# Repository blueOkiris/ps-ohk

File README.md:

# Polymath-Studio One-Handed Keyboard

## Description

Type with only one hand

Designed around

1) the most common letters used
2) relationships between sounds
3) the shape of a left hand
4) practicality

The PS-OHK (pronounced "psawk" [p͡sɑk̚]) aims to be the ultimate one-handed typing experience all without special modifiers (a standard key count) and a layout that is relatively easy to get used to.

## Build and Upload

Dependencies:

- arduino-cli
- make
- sdcc
- ch55xtool
- libusb

Build with `make -C fw`

Hold program button down, plug in, let go of program button, and run `make -C fw upload` within 3 seconds

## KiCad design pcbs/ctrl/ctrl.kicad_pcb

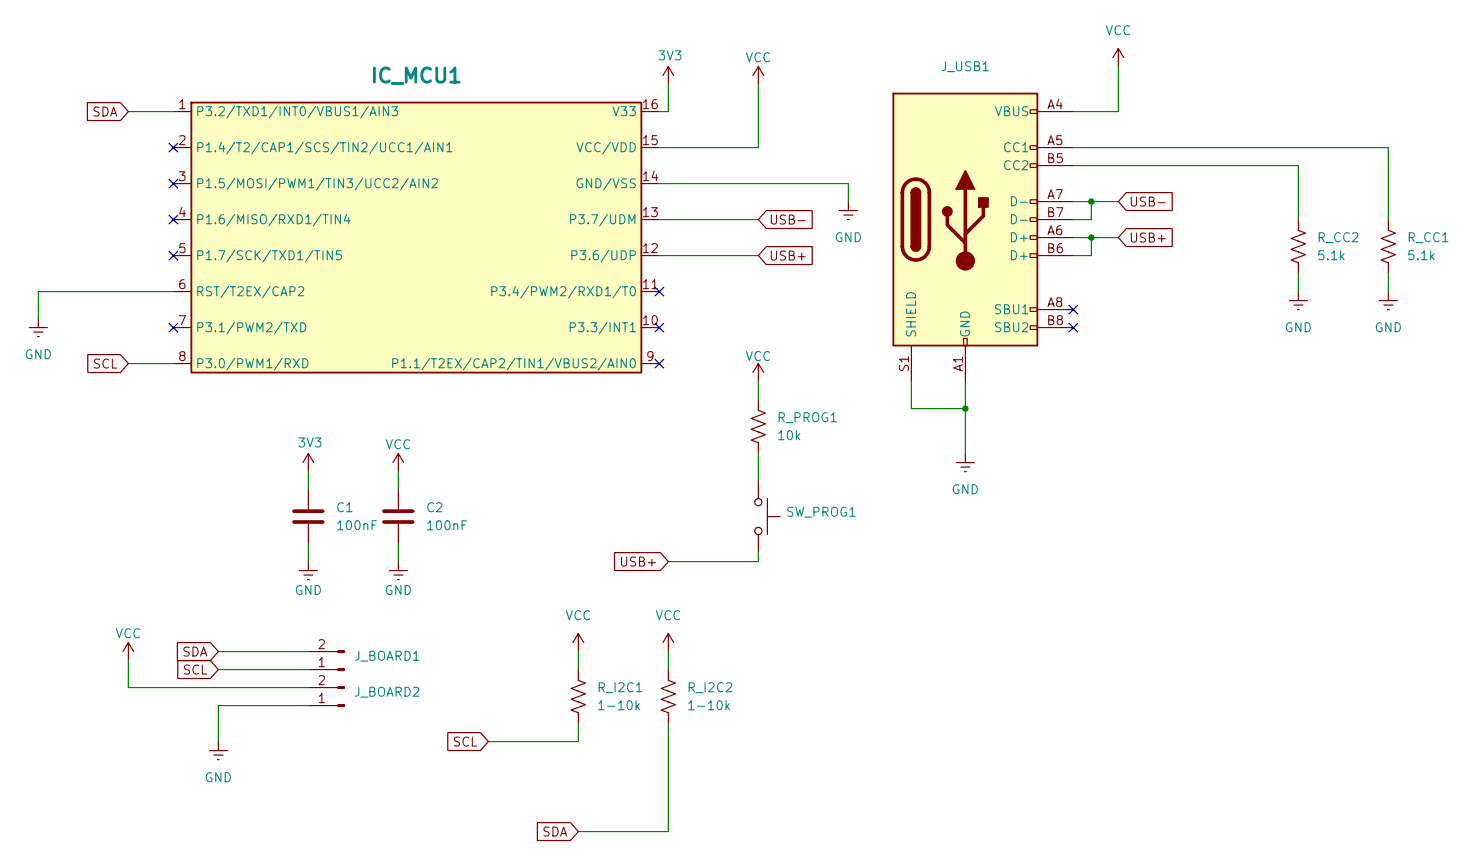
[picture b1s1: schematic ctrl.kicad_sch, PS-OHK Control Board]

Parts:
C1, C2: 100nF; C_0603_1608Metric
IC_MCU1: SOIC-16_3.9x9.9mm_Pitch1.27mm
J_BOARD1, J_BOARD2: PinHeader_1x02_P2.54mm_Vertical
J_USB1: USB_C_Receptacle_HCTL_HC-TYPE-C-16P-01A
R_CC1, R_CC2: 5.1k; R_0603_1608Metric
R_I2C1, R_I2C2: 1-10k; R_0603_1608Metric
R_PROG1: 10k; R_0603_1608Metric
SW_PROG1: SW_PUSH_6mm

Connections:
3V3: C1.1, IC_MCU1.16 (V33)
GND: C1.2, C2.2, IC_MCU1.6 (RST/T2EX/CAP2), IC_MCU1.14 (GND/VSS), J_BOARD2.1, J_USB1.A1 (GND), J_USB1.A12 (GND), J_USB1.B1 (GND), J_USB1.B12 (GND), J_USB1.S1 (SHIELD), R_CC1.2, R_CC2.2
unnamed: J_USB1.A5 (CC1), R_CC1.1
unnamed: J_USB1.B5 (CC2), R_CC2.1
unnamed: R_PROG1.2, SW_PROG1.1
SCL: IC_MCU1.8 (P3.0/PWM1/RXD), J_BOARD1.1, R_I2C1.2
SDA: IC_MCU1.1 (P3.2/TXD1/INT0/VBUS1/AIN3), J_BOARD1.2, R_I2C2.2
USB+: IC_MCU1.12 (P3.6/UDP), J_USB1.A6 (D+), J_USB1.B6 (D+), SW_PROG1.2
USB-: IC_MCU1.13 (P3.7/UDM), J_USB1.A7 (D-), J_USB1.B7 (D-)
VCC: C2.1, IC_MCU1.15 (VCC/VDD), J_BOARD2.2, J_USB1.A4 (VBUS), J_USB1.A9 (VBUS), J_USB1.B4 (VBUS), J_USB1.B9 (VBUS), R_I2C1.1, R_I2C2.1, R_PROG1.1

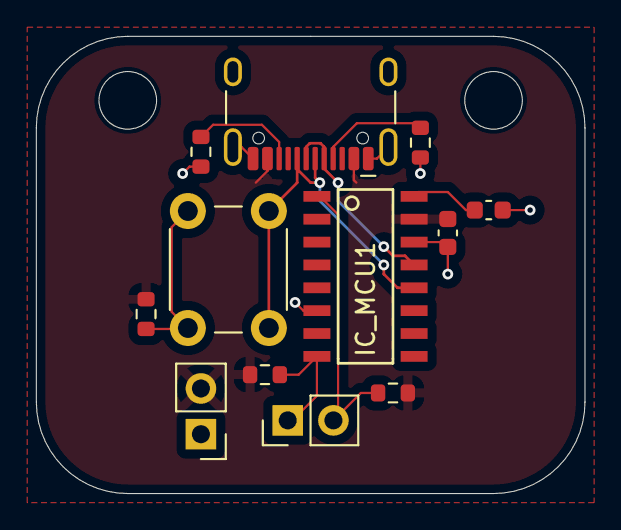
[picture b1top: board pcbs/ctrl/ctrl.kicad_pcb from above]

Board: 2 copper layers, 30.5 x 25.4 mm, 12 parts (0 on the bottom side), 10 nets.

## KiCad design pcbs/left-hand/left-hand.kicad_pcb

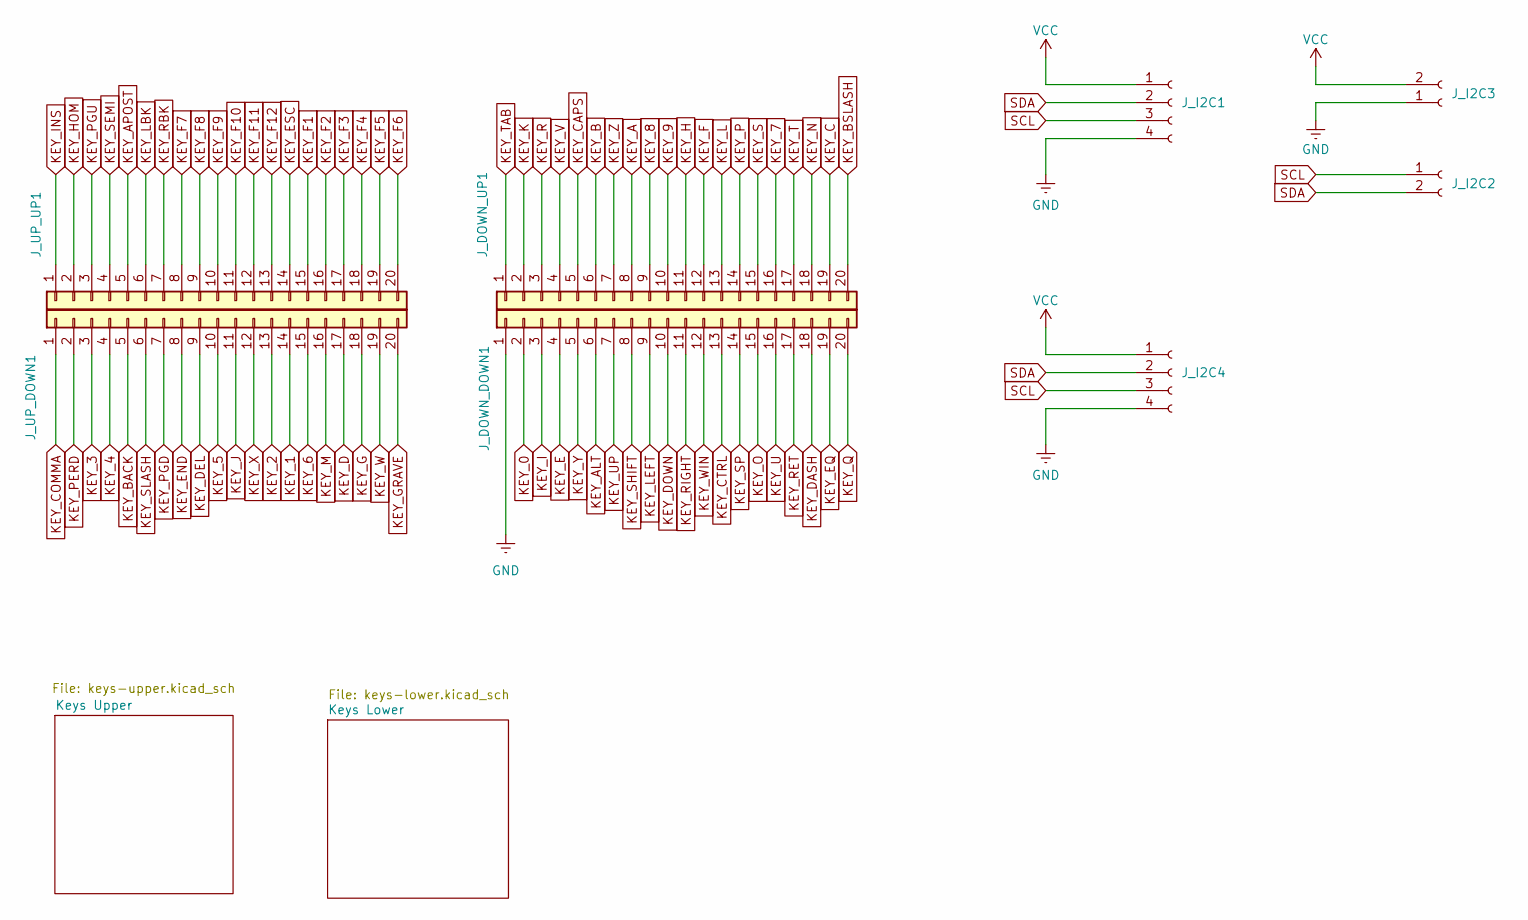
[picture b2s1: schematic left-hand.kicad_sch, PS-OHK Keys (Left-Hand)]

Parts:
J_DOWN_DOWN1: Conn_01x20; PinHeader_1x20_P2.54mm_Vertical
J_DOWN_UP1: Conn_01x20; PinHeader_1x20_P2.54mm_Vertical
J_I2C1, J_I2C4: Conn_01x04_Socket; PinHeader_1x04_P2.54mm_Vertical
J_I2C2, J_I2C3: Conn_01x04_Socket; PinHeader_1x02_P2.54mm_Vertical
J_UP_DOWN1: Conn_01x20; PinHeader_1x20_P2.54mm_Vertical
J_UP_UP1: Conn_01x20; PinHeader_1x20_P2.54mm_Vertical

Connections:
GND: J_DOWN_DOWN1.1, J_I2C1.4, J_I2C3.1, J_I2C4.4; also elsewhere on the board
KEY_0: J_DOWN_DOWN1.2; also elsewhere on the board
KEY_1: J_UP_DOWN1.14; also elsewhere on the board
KEY_2: J_UP_DOWN1.13; also elsewhere on the board
KEY_3: J_UP_DOWN1.3; also elsewhere on the board
KEY_4: J_UP_DOWN1.4; also elsewhere on the board
KEY_5: J_UP_DOWN1.10; also elsewhere on the board
KEY_6: J_UP_DOWN1.15; also elsewhere on the board
KEY_7: J_DOWN_UP1.16; also elsewhere on the board
KEY_8: J_DOWN_UP1.9; also elsewhere on the board
KEY_9: J_DOWN_UP1.10; also elsewhere on the board
KEY_A: J_DOWN_UP1.8; also elsewhere on the board
KEY_ALT: J_DOWN_DOWN1.6; also elsewhere on the board
KEY_APOST: J_UP_UP1.5; also elsewhere on the board
KEY_B: J_DOWN_UP1.6; also elsewhere on the board
KEY_BACK: J_UP_DOWN1.5; also elsewhere on the board
KEY_BSLASH: J_DOWN_UP1.20; also elsewhere on the board
KEY_C: J_DOWN_UP1.19; also elsewhere on the board
KEY_CAPS: J_DOWN_UP1.5; also elsewhere on the board
KEY_COMMA: J_UP_DOWN1.1; also elsewhere on the board
KEY_CTRL: J_DOWN_DOWN1.13; also elsewhere on the board
KEY_D: J_UP_DOWN1.17; also elsewhere on the board
KEY_DASH: J_DOWN_DOWN1.18; also elsewhere on the board
KEY_DEL: J_UP_DOWN1.9; also elsewhere on the board
KEY_DOWN: J_DOWN_DOWN1.10; also elsewhere on the board
KEY_E: J_DOWN_DOWN1.4; also elsewhere on the board
KEY_END: J_UP_DOWN1.8; also elsewhere on the board
KEY_EQ: J_DOWN_DOWN1.19; also elsewhere on the board
KEY_ESC: J_UP_UP1.14; also elsewhere on the board
KEY_F: J_DOWN_UP1.12; also elsewhere on the board
KEY_F1: J_UP_UP1.15; also elsewhere on the board
KEY_F2: J_UP_UP1.16; also elsewhere on the board
KEY_F3: J_UP_UP1.17; also elsewhere on the board
KEY_F4: J_UP_UP1.18; also elsewhere on the board
KEY_F5: J_UP_UP1.19; also elsewhere on the board
KEY_F6: J_UP_UP1.20; also elsewhere on the board
KEY_F7: J_UP_UP1.8; also elsewhere on the board
KEY_F8: J_UP_UP1.9; also elsewhere on the board
KEY_F9: J_UP_UP1.10; also elsewhere on the board
KEY_F10: J_UP_UP1.11; also elsewhere on the board
KEY_F11: J_UP_UP1.12; also elsewhere on the board
KEY_F12: J_UP_UP1.13; also elsewhere on the board
KEY_G: J_UP_DOWN1.18; also elsewhere on the board
KEY_GRAVE: J_UP_DOWN1.20; also elsewhere on the board
KEY_H: J_DOWN_UP1.11; also elsewhere on the board
KEY_HOM: J_UP_UP1.2; also elsewhere on the board
KEY_I: J_DOWN_DOWN1.3; also elsewhere on the board
KEY_INS: J_UP_UP1.1; also elsewhere on the board
KEY_J: J_UP_DOWN1.11; also elsewhere on the board
KEY_K: J_DOWN_UP1.2; also elsewhere on the board
KEY_L: J_DOWN_UP1.13; also elsewhere on the board
KEY_LBK: J_UP_UP1.6; also elsewhere on the board
KEY_LEFT: J_DOWN_DOWN1.9; also elsewhere on the board
KEY_M: J_UP_DOWN1.16; also elsewhere on the board
KEY_N: J_DOWN_UP1.18; also elsewhere on the board
KEY_O: J_DOWN_DOWN1.15; also elsewhere on the board
KEY_P: J_DOWN_UP1.14; also elsewhere on the board
KEY_PERD: J_UP_DOWN1.2; also elsewhere on the board
KEY_PGD: J_UP_DOWN1.7; also elsewhere on the board
KEY_PGU: J_UP_UP1.3; also elsewhere on the board
KEY_Q: J_DOWN_DOWN1.20; also elsewhere on the board
KEY_R: J_DOWN_UP1.3; also elsewhere on the board
KEY_RBK: J_UP_UP1.7; also elsewhere on the board
KEY_RET: J_DOWN_DOWN1.17; also elsewhere on the board
KEY_RIGHT: J_DOWN_DOWN1.11; also elsewhere on the board
KEY_S: J_DOWN_UP1.15; also elsewhere on the board
KEY_SEMI: J_UP_UP1.4; also elsewhere on the board
KEY_SHIFT: J_DOWN_DOWN1.8; also elsewhere on the board
KEY_SLASH: J_UP_DOWN1.6; also elsewhere on the board
KEY_SP: J_DOWN_DOWN1.14; also elsewhere on the board
KEY_T: J_DOWN_UP1.17; also elsewhere on the board
KEY_TAB: J_DOWN_UP1.1; also elsewhere on the board
KEY_U: J_DOWN_DOWN1.16; also elsewhere on the board
KEY_UP: J_DOWN_DOWN1.7; also elsewhere on the board
KEY_V: J_DOWN_UP1.4; also elsewhere on the board
KEY_W: J_UP_DOWN1.19; also elsewhere on the board
KEY_WIN: J_DOWN_DOWN1.12; also elsewhere on the board
KEY_X: J_UP_DOWN1.12; also elsewhere on the board
KEY_Y: J_DOWN_DOWN1.5; also elsewhere on the board
KEY_Z: J_DOWN_UP1.7; also elsewhere on the board
SCL: J_I2C1.3, J_I2C2.1, J_I2C4.3
SDA: J_I2C1.2, J_I2C2.2, J_I2C4.2
VCC: J_I2C1.1, J_I2C3.2, J_I2C4.1

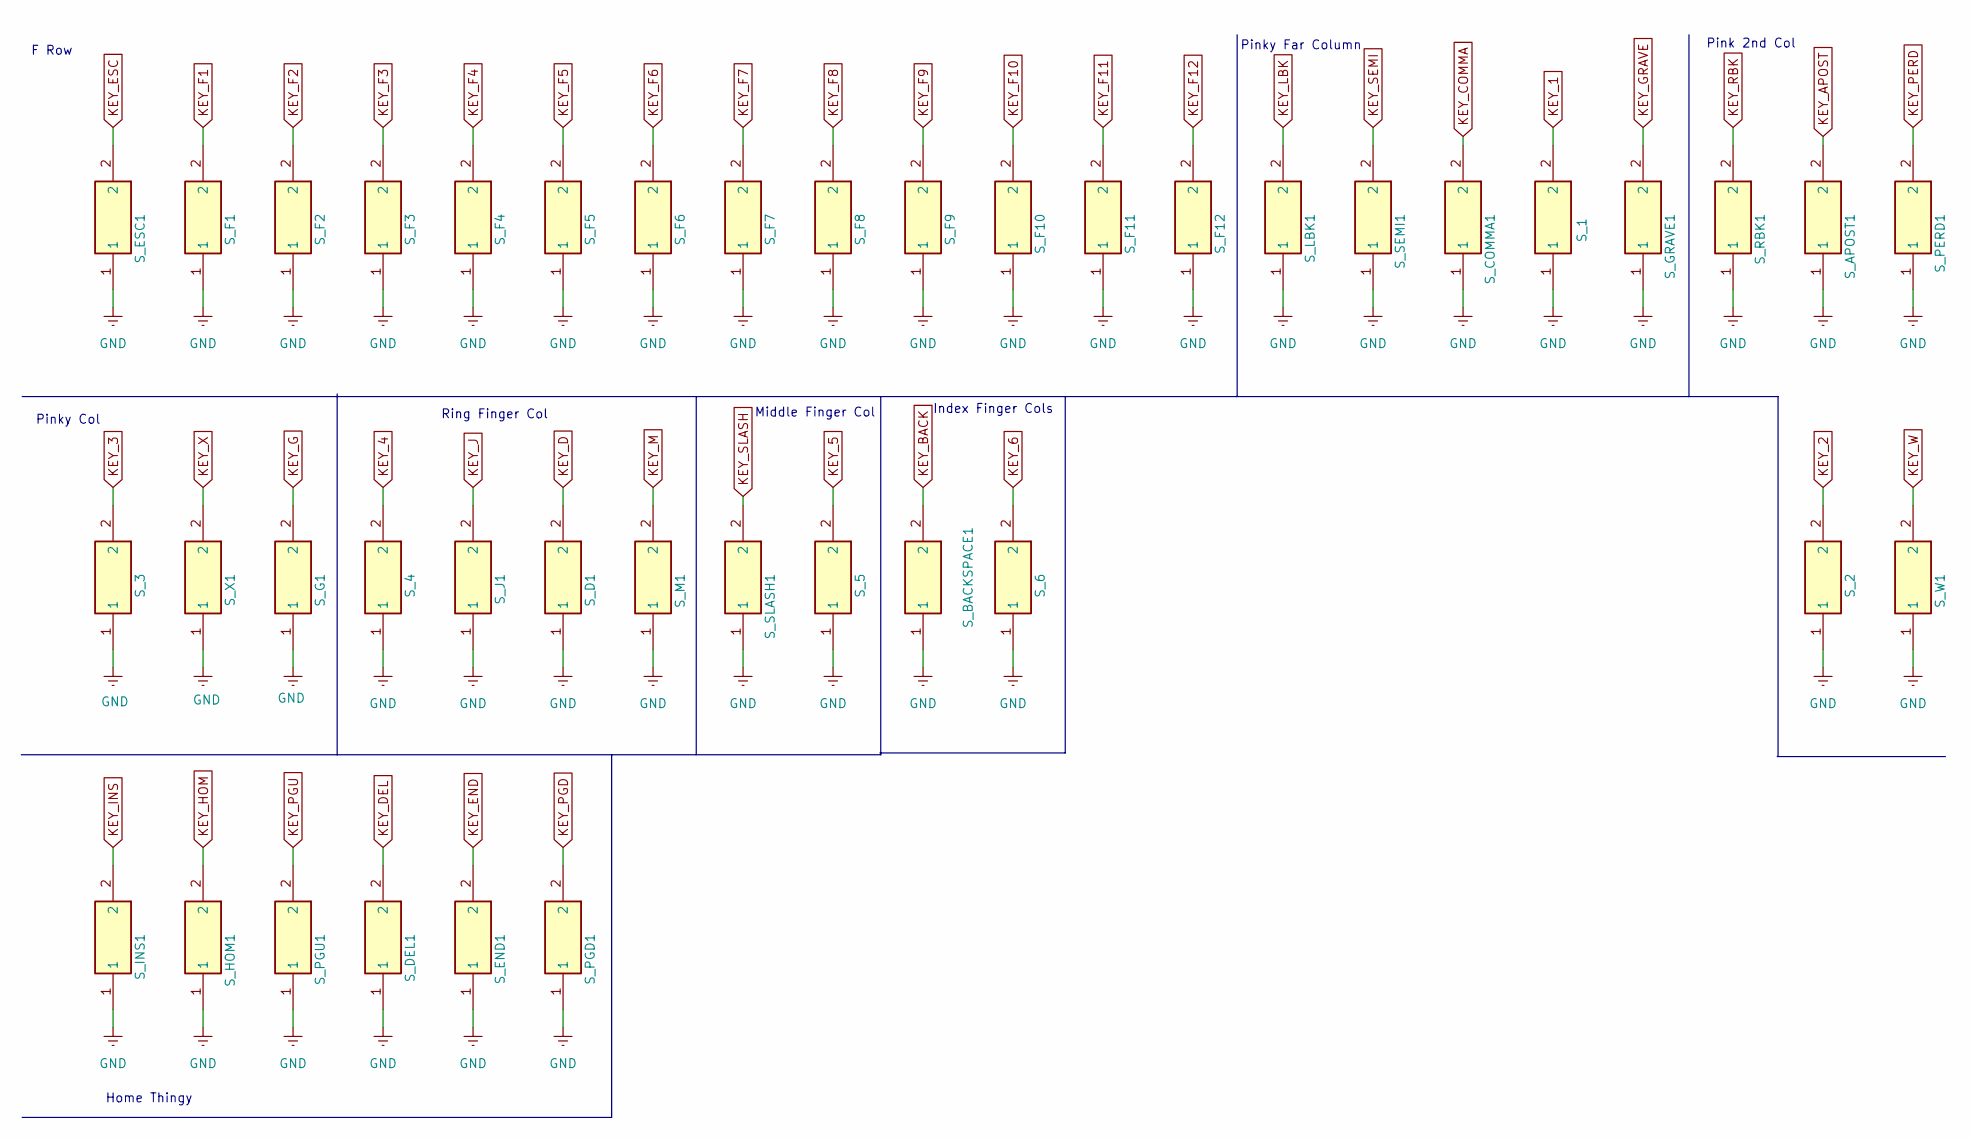
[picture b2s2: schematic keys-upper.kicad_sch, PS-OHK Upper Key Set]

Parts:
S_1, S_2, S_3, S_4, S_5, S_6: COM13834; Mouser Part Number 474-COM-13834
S_APOST1: COM13834; Mouser Part Number 474-COM-13834
S_BACKSPACE1: COM13834; Mouser Part Number 474-COM-13834
S_COMMA1: COM13834; Mouser Part Number 474-COM-13834
S_D1: COM13834; Mouser Part Number 474-COM-13834
S_DEL1: COM13834; Mouser Part Number 474-COM-13834
S_END1: COM13834; Mouser Part Number 474-COM-13834
S_ESC1: COM13834; Mouser Part Number 474-COM-13834
S_F1, S_F2, S_F3, S_F4, S_F5, S_F6, S_F7, S_F8, S_F9, S_F10, S_F11, S_F12: COM13834; Mouser Part Number 474-COM-13834
S_G1: COM13834; Mouser Part Number 474-COM-13834
S_GRAVE1: COM13834; Mouser Part Number 474-COM-13834
S_HOM1: COM13834; Mouser Part Number 474-COM-13834
S_INS1: COM13834; Mouser Part Number 474-COM-13834
S_J1: COM13834; Mouser Part Number 474-COM-13834
S_LBK1: COM13834; Mouser Part Number 474-COM-13834
S_M1: COM13834; Mouser Part Number 474-COM-13834
S_PERD1: COM13834; Mouser Part Number 474-COM-13834
S_PGD1: COM13834; Mouser Part Number 474-COM-13834
S_PGU1: COM13834; Mouser Part Number 474-COM-13834
S_RBK1: COM13834; Mouser Part Number 474-COM-13834
S_SEMI1: COM13834; Mouser Part Number 474-COM-13834
S_SLASH1: COM13834; Mouser Part Number 474-COM-13834
S_W1: COM13834; Mouser Part Number 474-COM-13834
S_X1: COM13834; Mouser Part Number 474-COM-13834

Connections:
GND: S_1.1, S_2.1, S_3.1, S_4.1, S_5.1, S_6.1, S_APOST1.1, S_BACKSPACE1.1, S_COMMA1.1, S_D1.1, S_DEL1.1, S_END1.1, S_ESC1.1, S_F1.1, S_F2.1, S_F3.1, S_F4.1, S_F5.1, S_F6.1, S_F7.1, S_F8.1, S_F9.1, S_F10.1, S_F11.1, S_F12.1, S_G1.1, S_GRAVE1.1, S_HOM1.1, S_INS1.1, S_J1.1, S_LBK1.1, S_M1.1, S_PERD1.1, S_PGD1.1, S_PGU1.1, S_RBK1.1, S_SEMI1.1, S_SLASH1.1, S_W1.1, S_X1.1; also elsewhere on the board
KEY_1: S_1.2; also elsewhere on the board
KEY_2: S_2.2; also elsewhere on the board
KEY_3: S_3.2; also elsewhere on the board
KEY_4: S_4.2; also elsewhere on the board
KEY_5: S_5.2; also elsewhere on the board
KEY_6: S_6.2; also elsewhere on the board
KEY_APOST: S_APOST1.2; also elsewhere on the board
KEY_BACK: S_BACKSPACE1.2; also elsewhere on the board
KEY_COMMA: S_COMMA1.2; also elsewhere on the board
KEY_D: S_D1.2; also elsewhere on the board
KEY_DEL: S_DEL1.2; also elsewhere on the board
KEY_END: S_END1.2; also elsewhere on the board
KEY_ESC: S_ESC1.2; also elsewhere on the board
KEY_F1: S_F1.2; also elsewhere on the board
KEY_F2: S_F2.2; also elsewhere on the board
KEY_F3: S_F3.2; also elsewhere on the board
KEY_F4: S_F4.2; also elsewhere on the board
KEY_F5: S_F5.2; also elsewhere on the board
KEY_F6: S_F6.2; also elsewhere on the board
KEY_F7: S_F7.2; also elsewhere on the board
KEY_F8: S_F8.2; also elsewhere on the board
KEY_F9: S_F9.2; also elsewhere on the board
KEY_F10: S_F10.2; also elsewhere on the board
KEY_F11: S_F11.2; also elsewhere on the board
KEY_F12: S_F12.2; also elsewhere on the board
KEY_G: S_G1.2; also elsewhere on the board
KEY_GRAVE: S_GRAVE1.2; also elsewhere on the board
KEY_HOM: S_HOM1.2; also elsewhere on the board
KEY_INS: S_INS1.2; also elsewhere on the board
KEY_J: S_J1.2; also elsewhere on the board
KEY_LBK: S_LBK1.2; also elsewhere on the board
KEY_M: S_M1.2; also elsewhere on the board
KEY_PERD: S_PERD1.2; also elsewhere on the board
KEY_PGD: S_PGD1.2; also elsewhere on the board
KEY_PGU: S_PGU1.2; also elsewhere on the board
KEY_RBK: S_RBK1.2; also elsewhere on the board
KEY_SEMI: S_SEMI1.2; also elsewhere on the board
KEY_SLASH: S_SLASH1.2; also elsewhere on the board
KEY_W: S_W1.2; also elsewhere on the board
KEY_X: S_X1.2; also elsewhere on the board

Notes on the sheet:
Pink 2nd Col
Middle Finger Col
Pinky Far Column
Pinky Col
Ring Finger Col
Index Finger Cols
Home Thingy
F Row

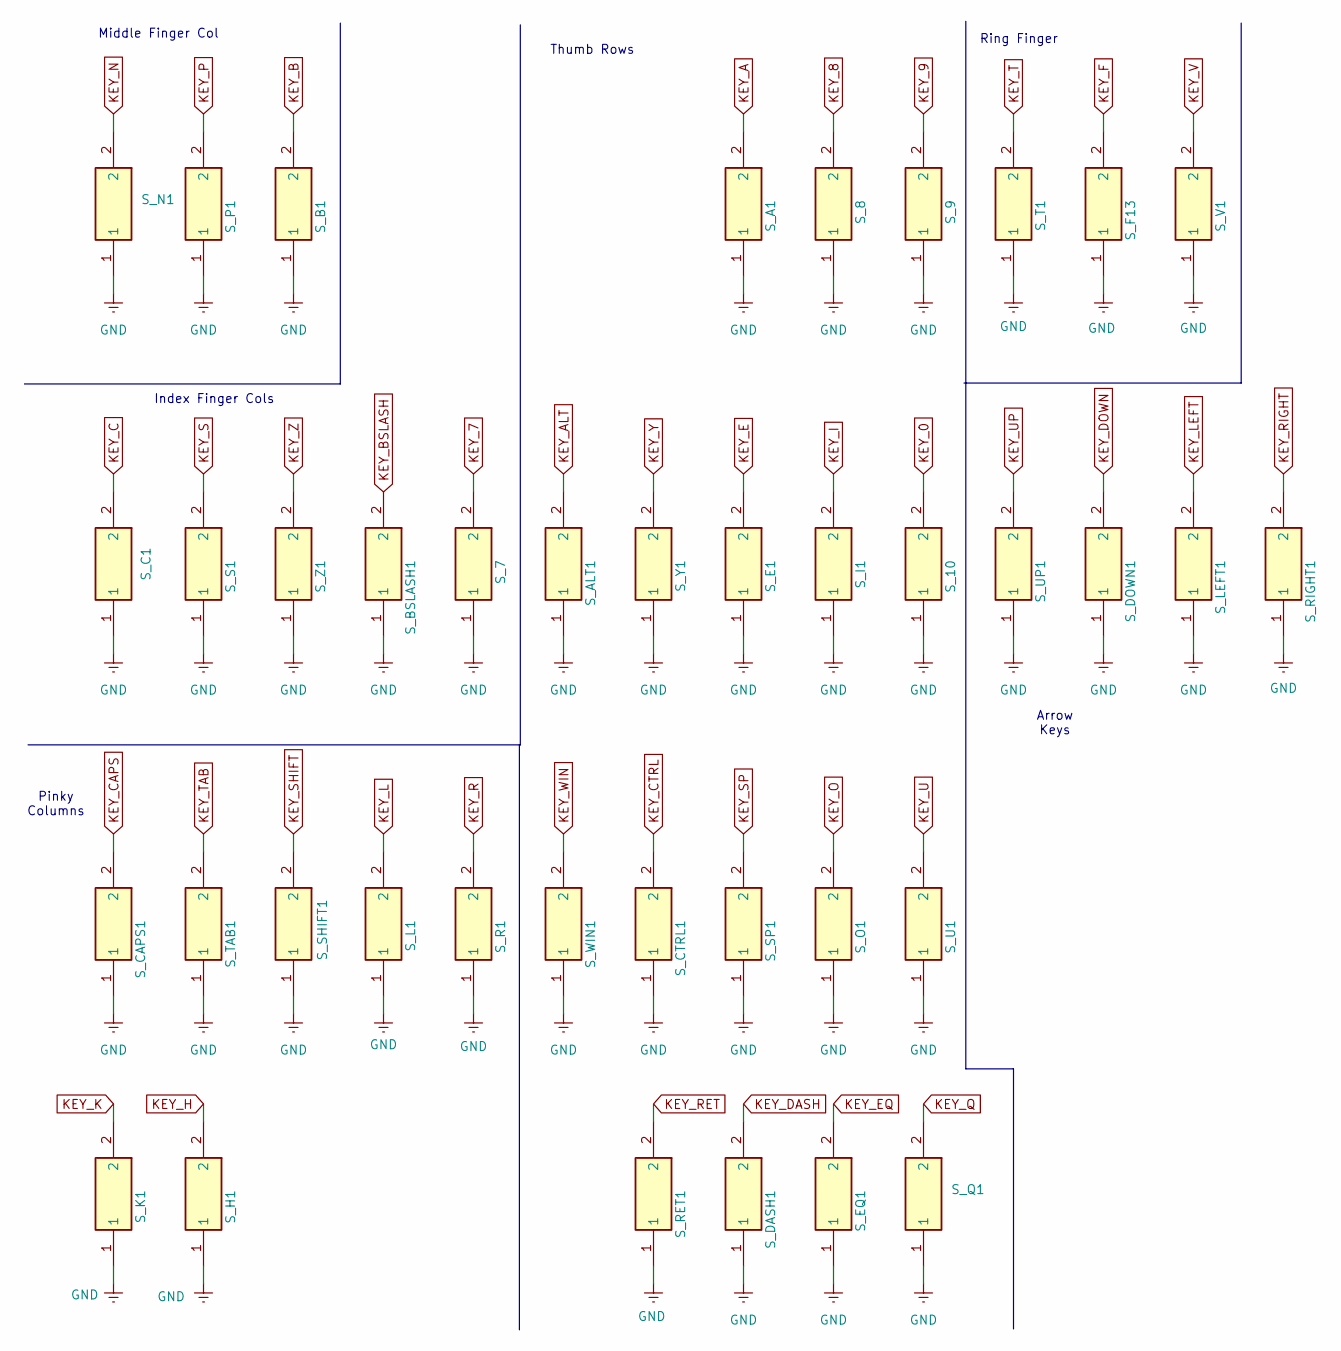
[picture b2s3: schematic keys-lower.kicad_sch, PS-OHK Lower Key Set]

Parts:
S_7, S_8, S_9, S_10: COM13834; Mouser Part Number 474-COM-13834
S_A1: COM13834; Mouser Part Number 474-COM-13834
S_ALT1: COM13834; Mouser Part Number 474-COM-13834
S_B1: COM13834; Mouser Part Number 474-COM-13834
S_BSLASH1: COM13834; Mouser Part Number 474-COM-13834
S_C1: COM13834; Mouser Part Number 474-COM-13834
S_CAPS1: COM13834; Mouser Part Number 474-COM-13834
S_CTRL1: COM13834; Mouser Part Number 474-COM-13834
S_DASH1: COM13834; Mouser Part Number 474-COM-13834
S_DOWN1: COM13834; Mouser Part Number 474-COM-13834
S_E1: COM13834; Mouser Part Number 474-COM-13834
S_EQ1: COM13834; Mouser Part Number 474-COM-13834
S_F13: COM13834; Mouser Part Number 474-COM-13834
S_H1: COM13834; Mouser Part Number 474-COM-13834
S_I1: COM13834; Mouser Part Number 474-COM-13834
S_K1: COM13834; Mouser Part Number 474-COM-13834
S_L1: COM13834; Mouser Part Number 474-COM-13834
S_LEFT1: COM13834; Mouser Part Number 474-COM-13834
S_N1: COM13834; Mouser Part Number 474-COM-13834
S_O1: COM13834; Mouser Part Number 474-COM-13834
S_P1: COM13834; Mouser Part Number 474-COM-13834
S_Q1: COM13834; Mouser Part Number 474-COM-13834
S_R1: COM13834; Mouser Part Number 474-COM-13834
S_RET1: COM13834; Mouser Part Number 474-COM-13834
S_RIGHT1: COM13834; Mouser Part Number 474-COM-13834
S_S1: COM13834; Mouser Part Number 474-COM-13834
S_SHIFT1: COM13834; Mouser Part Number 474-COM-13834
S_SP1: COM13834; Mouser Part Number 474-COM-13834
S_T1: COM13834; Mouser Part Number 474-COM-13834
S_TAB1: COM13834; Mouser Part Number 474-COM-13834
S_U1: COM13834; Mouser Part Number 474-COM-13834
S_UP1: COM13834; Mouser Part Number 474-COM-13834
S_V1: COM13834; Mouser Part Number 474-COM-13834
S_WIN1: COM13834; Mouser Part Number 474-COM-13834
S_Y1: COM13834; Mouser Part Number 474-COM-13834
S_Z1: COM13834; Mouser Part Number 474-COM-13834

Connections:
GND: S_7.1, S_8.1, S_9.1, S_10.1, S_A1.1, S_ALT1.1, S_B1.1, S_BSLASH1.1, S_C1.1, S_CAPS1.1, S_CTRL1.1, S_DASH1.1, S_DOWN1.1, S_E1.1, S_EQ1.1, S_F13.1, S_H1.1, S_I1.1, S_K1.1, S_L1.1, S_LEFT1.1, S_N1.1, S_O1.1, S_P1.1, S_Q1.1, S_R1.1, S_RET1.1, S_RIGHT1.1, S_S1.1, S_SHIFT1.1, S_SP1.1, S_T1.1, S_TAB1.1, S_U1.1, S_UP1.1, S_V1.1, S_WIN1.1, S_Y1.1, S_Z1.1; also elsewhere on the board
KEY_0: S_10.2; also elsewhere on the board
KEY_7: S_7.2; also elsewhere on the board
KEY_8: S_8.2; also elsewhere on the board
KEY_9: S_9.2; also elsewhere on the board
KEY_A: S_A1.2; also elsewhere on the board
KEY_ALT: S_ALT1.2; also elsewhere on the board
KEY_B: S_B1.2; also elsewhere on the board
KEY_BSLASH: S_BSLASH1.2; also elsewhere on the board
KEY_C: S_C1.2; also elsewhere on the board
KEY_CAPS: S_CAPS1.2; also elsewhere on the board
KEY_CTRL: S_CTRL1.2; also elsewhere on the board
KEY_DASH: S_DASH1.2; also elsewhere on the board
KEY_DOWN: S_DOWN1.2; also elsewhere on the board
KEY_E: S_E1.2; also elsewhere on the board
KEY_EQ: S_EQ1.2; also elsewhere on the board
KEY_F: S_F13.2; also elsewhere on the board
KEY_H: S_H1.2; also elsewhere on the board
KEY_I: S_I1.2; also elsewhere on the board
KEY_K: S_K1.2; also elsewhere on the board
KEY_L: S_L1.2; also elsewhere on the board
KEY_LEFT: S_LEFT1.2; also elsewhere on the board
KEY_N: S_N1.2; also elsewhere on the board
KEY_O: S_O1.2; also elsewhere on the board
KEY_P: S_P1.2; also elsewhere on the board
KEY_Q: S_Q1.2; also elsewhere on the board
KEY_R: S_R1.2; also elsewhere on the board
KEY_RET: S_RET1.2; also elsewhere on the board
KEY_RIGHT: S_RIGHT1.2; also elsewhere on the board
KEY_S: S_S1.2; also elsewhere on the board
KEY_SHIFT: S_SHIFT1.2; also elsewhere on the board
KEY_SP: S_SP1.2; also elsewhere on the board
KEY_T: S_T1.2; also elsewhere on the board
KEY_TAB: S_TAB1.2; also elsewhere on the board
KEY_U: S_U1.2; also elsewhere on the board
KEY_UP: S_UP1.2; also elsewhere on the board
KEY_V: S_V1.2; also elsewhere on the board
KEY_WIN: S_WIN1.2; also elsewhere on the board
KEY_Y: S_Y1.2; also elsewhere on the board
KEY_Z: S_Z1.2; also elsewhere on the board

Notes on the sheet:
Arrow Keys
Index Finger Cols
Pinky Columns
Thumb Rows
Ring Finger
Middle Finger Col

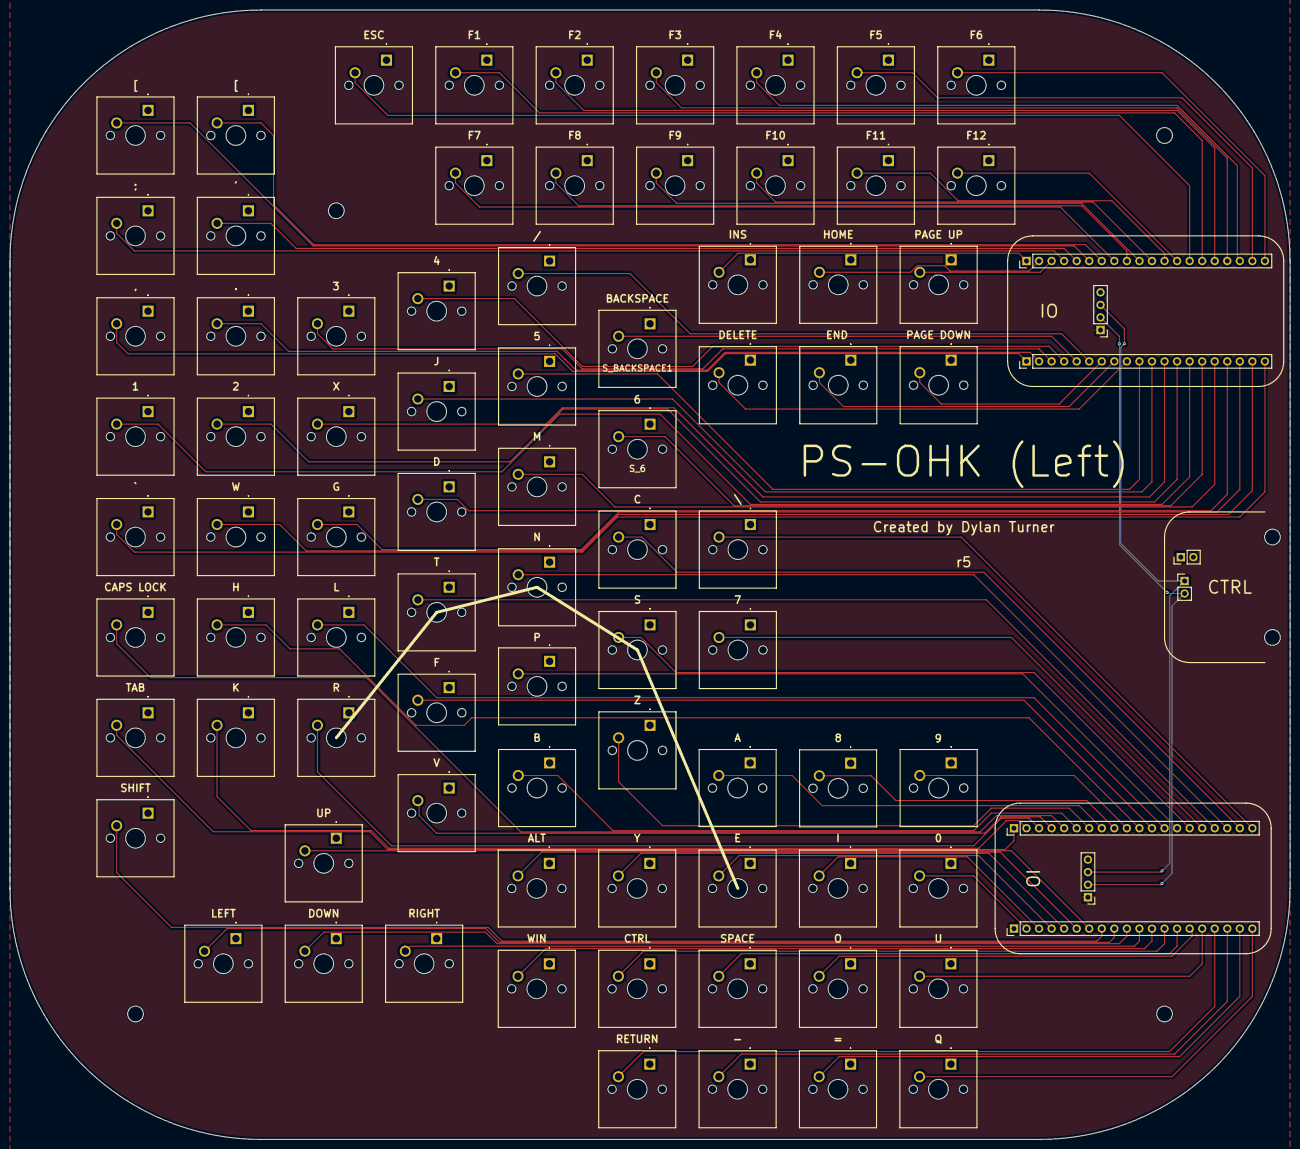
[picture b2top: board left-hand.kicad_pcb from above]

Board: 2 copper layers, 259.1 x 228.6 mm, 87 parts (0 on the bottom side), 83 nets.

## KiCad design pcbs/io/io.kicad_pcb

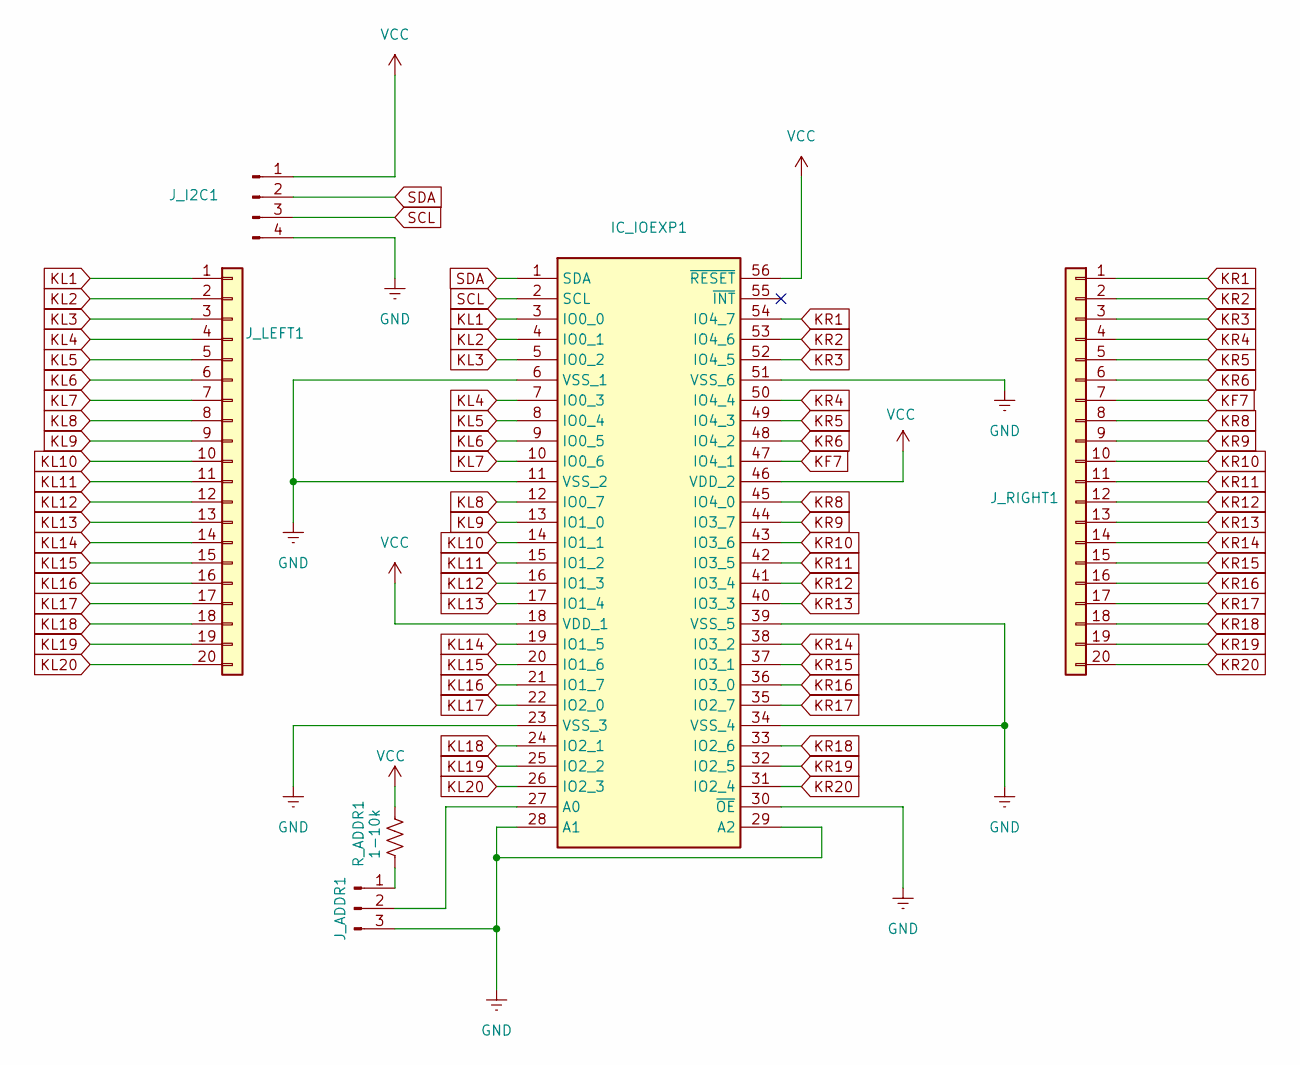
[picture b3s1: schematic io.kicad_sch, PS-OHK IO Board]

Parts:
IC_IOEXP1: SOP50P810X120-56N; Mouser Part Number 771-PCA9505DGGY
J_ADDR1: Conn_01x03_Pin; PinHeader_1x03_P2.54mm_Vertical
J_I2C1: Conn_01x04_Pin; PinHeader_1x04_P2.54mm_Vertical
J_LEFT1: Conn_01x20; PinHeader_1x20_P2.54mm_Vertical
J_RIGHT1: Conn_01x20; PinHeader_1x20_P2.54mm_Vertical
R_ADDR1: 1-10k; R_0603_1608Metric

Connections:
GND: IC_IOEXP1.6 (VSS_1), IC_IOEXP1.11 (VSS_2), IC_IOEXP1.23 (VSS_3), IC_IOEXP1.28 (A1), IC_IOEXP1.29 (A2), IC_IOEXP1.30 (~OE), IC_IOEXP1.34 (VSS_4), IC_IOEXP1.39 (VSS_5), IC_IOEXP1.51 (VSS_6), J_ADDR1.3, J_I2C1.4
KF7: IC_IOEXP1.47 (IO4_1), J_RIGHT1.7
KL1: IC_IOEXP1.3 (IO0_0), J_LEFT1.1
KL2: IC_IOEXP1.4 (IO0_1), J_LEFT1.2
KL3: IC_IOEXP1.5 (IO0_2), J_LEFT1.3
KL4: IC_IOEXP1.7 (IO0_3), J_LEFT1.4
KL5: IC_IOEXP1.8 (IO0_4), J_LEFT1.5
KL6: IC_IOEXP1.9 (IO0_5), J_LEFT1.6
KL7: IC_IOEXP1.10 (IO0_6), J_LEFT1.7
KL8: IC_IOEXP1.12 (IO0_7), J_LEFT1.8
KL9: IC_IOEXP1.13 (IO1_0), J_LEFT1.9
KL10: IC_IOEXP1.14 (IO1_1), J_LEFT1.10
KL11: IC_IOEXP1.15 (IO1_2), J_LEFT1.11
KL12: IC_IOEXP1.16 (IO1_3), J_LEFT1.12
KL13: IC_IOEXP1.17 (IO1_4), J_LEFT1.13
KL14: IC_IOEXP1.19 (IO1_5), J_LEFT1.14
KL15: IC_IOEXP1.20 (IO1_6), J_LEFT1.15
KL16: IC_IOEXP1.21 (IO1_7), J_LEFT1.16
KL17: IC_IOEXP1.22 (IO2_0), J_LEFT1.17
KL18: IC_IOEXP1.24 (IO2_1), J_LEFT1.18
KL19: IC_IOEXP1.25 (IO2_2), J_LEFT1.19
KL20: IC_IOEXP1.26 (IO2_3), J_LEFT1.20
KR1: IC_IOEXP1.54 (IO4_7), J_RIGHT1.1
KR2: IC_IOEXP1.53 (IO4_6), J_RIGHT1.2
KR3: IC_IOEXP1.52 (IO4_5), J_RIGHT1.3
KR4: IC_IOEXP1.50 (IO4_4), J_RIGHT1.4
KR5: IC_IOEXP1.49 (IO4_3), J_RIGHT1.5
KR6: IC_IOEXP1.48 (IO4_2), J_RIGHT1.6
KR8: IC_IOEXP1.45 (IO4_0), J_RIGHT1.8
KR9: IC_IOEXP1.44 (IO3_7), J_RIGHT1.9
KR10: IC_IOEXP1.43 (IO3_6), J_RIGHT1.10
KR11: IC_IOEXP1.42 (IO3_5), J_RIGHT1.11
KR12: IC_IOEXP1.41 (IO3_4), J_RIGHT1.12
KR13: IC_IOEXP1.40 (IO3_3), J_RIGHT1.13
KR14: IC_IOEXP1.38 (IO3_2), J_RIGHT1.14
KR15: IC_IOEXP1.37 (IO3_1), J_RIGHT1.15
KR16: IC_IOEXP1.36 (IO3_0), J_RIGHT1.16
KR17: IC_IOEXP1.35 (IO2_7), J_RIGHT1.17
KR18: IC_IOEXP1.33 (IO2_6), J_RIGHT1.18
KR19: IC_IOEXP1.32 (IO2_5), J_RIGHT1.19
KR20: IC_IOEXP1.31 (IO2_4), J_RIGHT1.20
unnamed: IC_IOEXP1.27 (A0), J_ADDR1.2
unnamed: J_ADDR1.1, R_ADDR1.2
SCL: IC_IOEXP1.2 (SCL), J_I2C1.3
SDA: IC_IOEXP1.1 (SDA), J_I2C1.2
VCC: IC_IOEXP1.18 (VDD_1), IC_IOEXP1.46 (VDD_2), IC_IOEXP1.56 (~RESET), J_I2C1.1, R_ADDR1.1

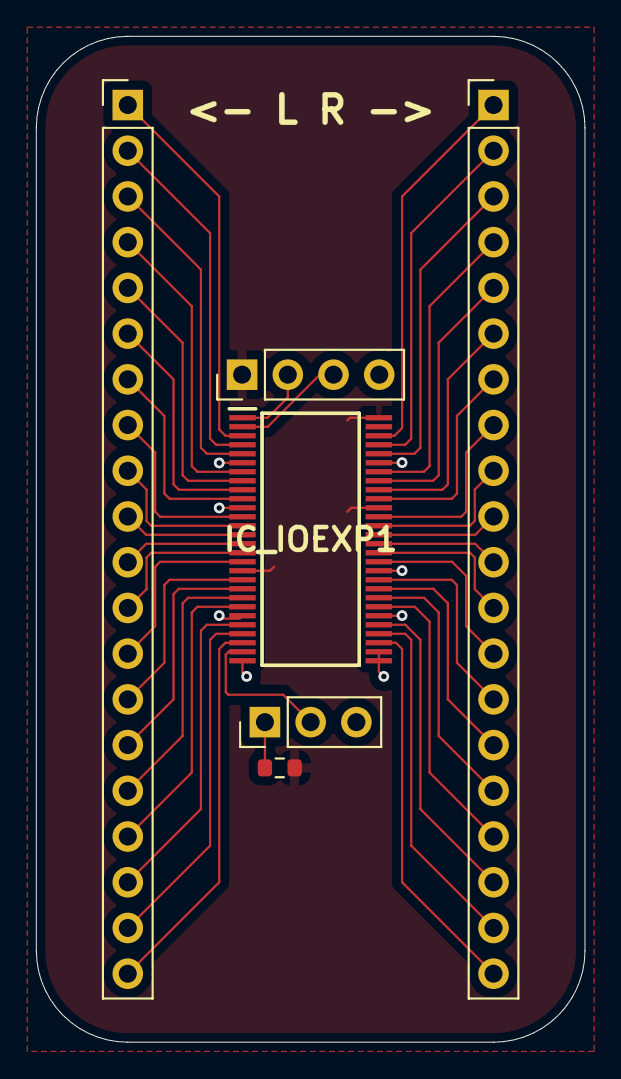
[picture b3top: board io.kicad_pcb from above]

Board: 2 copper layers, 30.5 x 55.9 mm, 6 parts (0 on the bottom side), 46 nets.
